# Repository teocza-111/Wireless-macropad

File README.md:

# Wireless-macropad
It's a basic 3x3 keyboard with bluetooth connectivity and a rotary encoder built on ZMK firmware.
## Quick note for forge reviewers:
This project was fully funded by stasis I'm moving this here since I plan to make my future projects on forge 
## It features a(n):
- nrf52840 microcontroller
- Seeed 106990290 lipo charger
- EC11E Rotary Encoder w/ switch
- Li-Po Battery 4000mah
### Why?
I like simracing but i needed some extra keybinds so i made my first vesion of this project but it was annoying that there was an extra cable on my desk so now im making it wireless.
# Media

# BoM
|Part Name                                                                                                            |Qty.|Cost (per part/batch) in PLN|Cost (total) in PLN|Link                                                |
|---------------------------------------------------------------------------------------------------------------------|----|----------------------------|-------------------|----------------------------------------------------|
|nrf52840 microcontroller                                                                                             |1   |15,89zł                     |14,79zł            |https://pl.aliexpress.com/item/1005009516681283.html|
|Seeed 106990290 (lipo charger)                                                                                       |1   |29,29zł                     |29,29zł            |https://pl.aliexpress.com/item/4000572310671.html   |
|1N4148 Diodes                                                                                                        |9   |4,79zł                      |4,79zł             |https://pl.aliexpress.com/item/1005006245109375.html|
|Cherry MX switches                                                                                                   |8   |9,07zł                      |9,07zł             |https://pl.aliexpress.com/item/1005010462521108.html|
|EC11E Rotary Encoder w/ switch                                                                                       |1   |12,59zł                     |12,59zł            |https://pl.aliexpress.com/item/1005005983134515.html|
|Li-Po Battery 5000mah                                                                                                |1   |30,69zł                     |30,69zł            |https://pl.aliexpress.com/item/1005010088690191.html|
|JST PH 2.0mm connector                                                                                               |1   |6,03zł                      |6,03zł             |https://pl.aliexpress.com/item/1005004955655144.html|
|Keycaps                                                                                                              |8   |15,50zł                     |15,50zł            |https://pl.aliexpress.com/item/1005002906017844.html|
|Neodymium magnets 4x2mm                                                                                              |16  |9,06zł                      |9,06zł             |https://pl.aliexpress.com/item/1005010075244557.html|
|ALL PRICES IN PLN!!!                                                                                                 |    |Total cost is →             |131,81zł           |                                                    |
|Note:                                                                                                                |    |                            |                   |                                                    |
|Things that are usually bought in bulk (diodes switches etc.) come in packs of for example 50 even if you only need 5|    |                            |                   |                                                    |

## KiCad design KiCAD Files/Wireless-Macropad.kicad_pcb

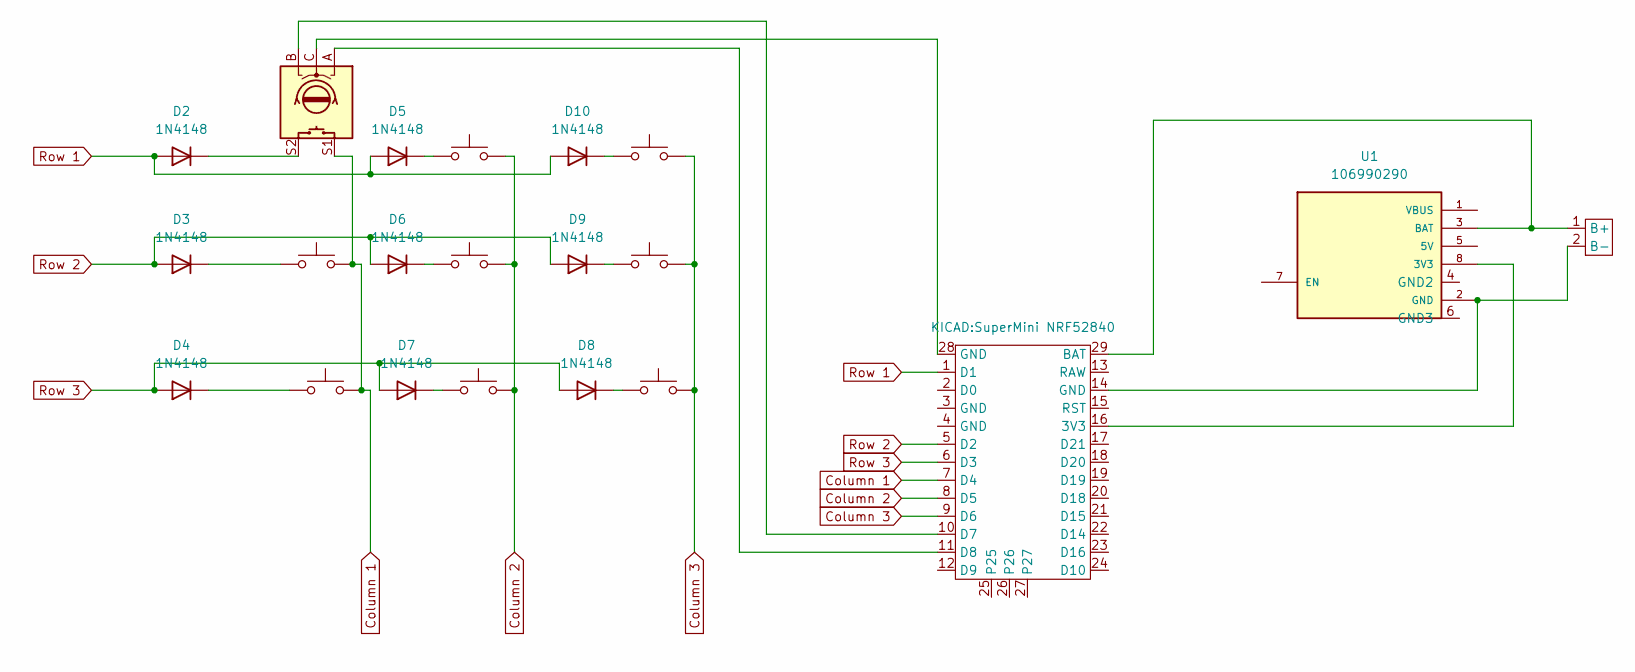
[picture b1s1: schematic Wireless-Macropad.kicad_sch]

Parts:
D2, D3, D4, D5, D6, D7, D8, D9, D10: 1N4148; D_DO-35_SOD27_P7.62mm_Horizontal
SW1: RotaryEncoder_Switch; RotaryEncoder_Alps_EC11E-Switch_Vertical_H20mm
SW2, SW3, SW4, SW5, SW6, SW7, SW8, SW9: SW_Push; SW_Cherry_MX_1.00u_PCB
U1: 106990290; MODULE_106990290; PARTREV NA
U2: SuperMini NRF52840
U3: JST_PH_S2B-PH-K_1x02_P2.00mm_Horizontal

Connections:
Column 1: SW1.S1, SW4.2, SW7.2, U2.7 (D4)
Column 2: SW2.2, SW5.2, SW8.2, U2.8 (D5)
Column 3: SW3.2, SW6.2, SW9.2, U2.9 (D6)
GND: U1.2 (GND), U1.4 (GND), U1.6 (GND), U2.14 (GND), U3.2 (B-)
unnamed: D2.1 (K), SW1.S2
unnamed: D3.1 (K), SW4.1
unnamed: D4.1 (K), SW7.1
unnamed: D5.1 (K), SW2.1
unnamed: D6.1 (K), SW5.1
unnamed: D7.1 (K), SW8.1
unnamed: D8.1 (K), SW9.1
unnamed: D9.1 (K), SW6.1
unnamed: D10.1 (K), SW3.1
unnamed: SW1.C, U2.28 (GND)
unnamed: U1.8 (3V3), U2.16 (3V3)
unnamed: U1.3 (BAT), U2.29 (BAT), U3.1 (B+)
unnamed: SW1.B, U2.10 (D7)
unnamed: SW1.A, U2.11 (D8)
Row 1: D2.2 (A), D5.2 (A), D10.2 (A), U2.1 (D1)
Row 2: D3.2 (A), D6.2 (A), D9.2 (A), U2.5 (D2)
Row 3: D4.2 (A), D7.2 (A), D8.2 (A), U2.6 (D3)

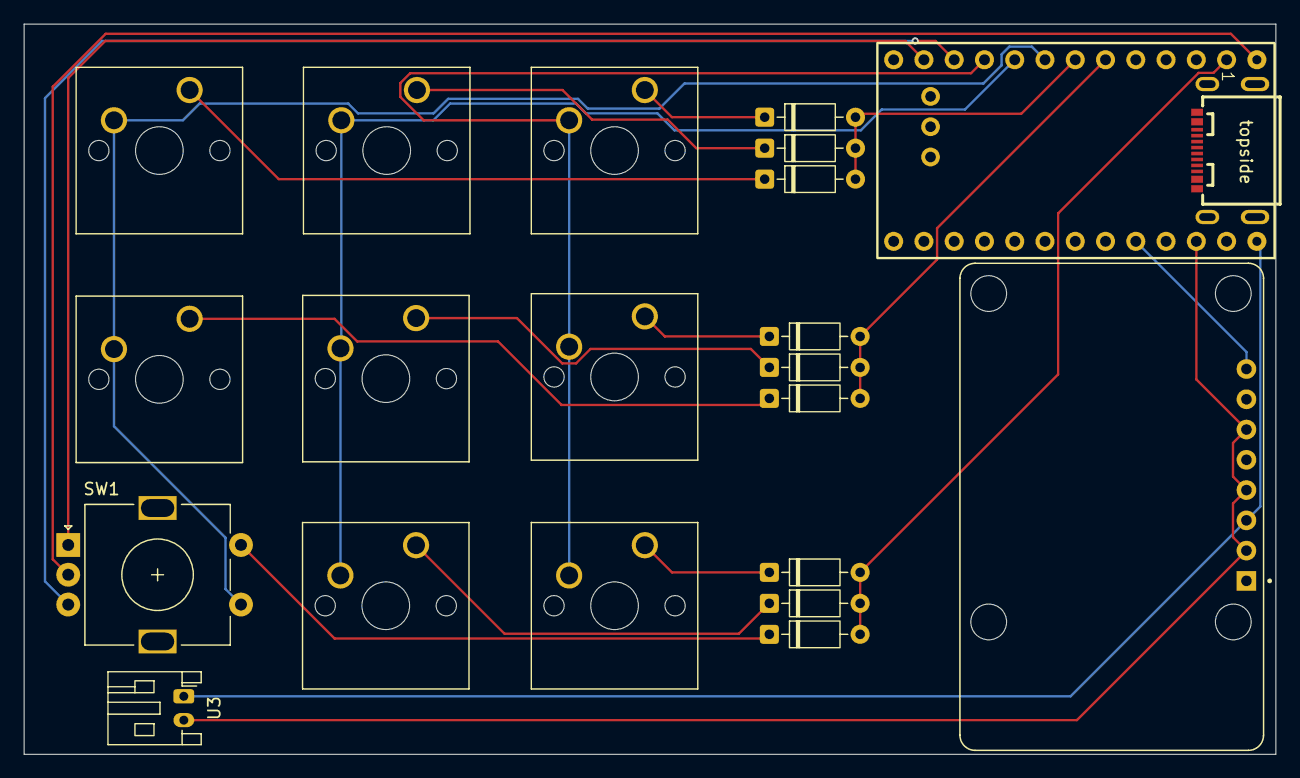
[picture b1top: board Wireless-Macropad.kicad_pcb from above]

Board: 2 copper layers, 105.1 x 61.3 mm, 21 parts (0 on the bottom side), 21 nets.

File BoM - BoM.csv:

Part Name,Qty.,Cost (per part) in PLN,Cost (total) in PLN,Link
nrf52840 microcontroller,1,"11,99PLN","11,99PLN",https://www.aliexpress.com/ssr/300000512/BundleDeals2?spm=a2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
Seeed 106990290 (lipo charger),1,"28,49PLN","28,49PLN",https://www.aliexpress.com/p/tesla-landing/index.html?scenar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
1N4148 Diodes,9,"4,69PLN","4,69PLN",https://pl.aliexpress.com/item/1005006245109375.html?spm=a2g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
Cherry MX switches,8,"9,69PLN","9,69PLN",https://pl.aliexpress.com/item/1005010462521108.html?spm=a2g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
EC11E Rotary Encoder w/ switch,1,"12,23PLN","12,23PLN",https://pl.aliexpress.com/item/1005005983134515.html?spm=a2g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
SPDT switch,1,"2,17PLN","2,17PLN",https://pl.aliexpress.com/item/1005006875320699.html?spm=a2g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
JST PH 2.0mm connector,1,"5,89PLN","5,89PLN",https://pl.aliexpress.com/item/1005004955655144.html?spm=a2g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
Li-Po Battery (im using 800mah),1,"22,09PLN","22,09PLN",https://pl.aliexpress.com/item/1005007942937452.html?spm=a2g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
,,,,
ALL PRICES IN PLN!!!,,,,
Note:,,,,
Things that are usually bought in bulk (diodes switches etc.) come in packs of for example 50 even if you only need 5,,,,

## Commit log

2026-03-02 Added a BoM and finished designing my pcb.
2026-03-02 Added some screenshots
2026-03-02 Enhance README with project details and images
    Added a description and media section to the README.
2026-03-04 Updated my PCB and generated my gerber file
2026-03-04 Added firmware and updated design
    Firmware made using ZMK, also updated BoM to match current parts
2026-03-06 Made the case
2026-03-06 Updated BoM.csv
2026-03-06 updated readme rq
2026-03-06 Update Li-Po Battery capacity in README
2026-03-06 Add motivation section to README
    Added a section explaining the motivation behind the project.
2026-03-06 Correct grammar in features section of README
2026-03-06 Update README.md
    Expanded description of the keyboard to include ZMK firmware.
2026-03-21 Added full render + .f3z file
    Couldnt export it in .step for some reason fusion 360 just crashed
2026-03-21 Fix image filename in README
    Corrected image filename in README from 'full.png' to 'Full.png'.
2026-03-21 Update BoM with new parts and prices
2026-03-21 Updated BoM with correct links
2026-04-27 Add Bill of Materials section to README
    Added a Bill of Materials (BoM) section with details on parts, quantities, costs, and links.
2026-04-27 Added teh gerber file
2026-05-30 Added a journal
    Journal exported from stasis
2026-05-30 Add additional images to README Media section
    Added two new images to the Media section of the README.
2026-06-06 Revise JOURNAL.md for clarity and organization
    Rewrote the journal entries for clarity and fixed image duplication issues. Updated project progress and timeline.
